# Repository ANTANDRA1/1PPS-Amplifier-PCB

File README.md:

# 1PPS-Amplifier-PCB
1PPS signal buffer/inverter PCB for u-blox M8N GPS with 50 Ohm output
# Плата підсилення сигналу 1PPS

Плата призначена для буферизації та інвертування сигналу **1PPS від GPS-приймача u-blox M8N**.

Плата приймає логічний сигнал 1PPS від GPS-модуля, буферизує та інвертує його за допомогою логічного інвертора **74LVC1G04**, після чого передає сигнал на вихід через **BNC-роз’єм з узгодженням під 50 Ом**.

## Основні можливості

- вхід сигналу 1PPS від GPS-приймача;
- живлення 3.3 В;
- швидкодіючий логічний інвертор 74LVC1G04;
- інвертований вихід 1PPS;
- послідовне узгодження виходу для роботи з 50-омною лінією;
- вихід через BNC female PCB;
- вхід через Dupont 2.54 мм;
- роз’єм живлення Dupont 2.54 мм;
- розв’язувальний конденсатор 100 нФ;
- одностороння розводка плати;
- полігон GND;
- монтажні отвори під гвинти M2;
- підписи роз’ємів і контактів на шовкографії плати.

## Сигнальний тракт

```text
GPS 1PPS
   |
   v
J1 - 1PPS IN
   |
R1 - 100 Ом
   |
U1 - 74LVC1G04
   |
R2 - 33 Ом
   |
J4 - BNC 1PPS OUT
```

Мікросхема **74LVC1G04** виконує буферизацію та інвертування сигналу.

Резистор R2 використовується для послідовного узгодження виходу. Разом із власним вихідним опором логічного драйвера він формує вихід, придатний для підключення до лінії з хвильовим опором 50 Ом.

## Живлення

Плата живиться від напруги **3.3 В**.

Роз’єм живлення J2:

| Контакт | Сигнал |
|---|---|
| 1 | +3.3 V |
| 2 | GND |

Біля мікросхеми U1 встановлений розв’язувальний конденсатор **C1 100 нФ**.

## Роз’єми

### J1 — вхід 1PPS

Роз’єм Dupont 2.54 мм на 2 контакти.

| Контакт | Сигнал |
|---|---|
| 1 | 1PPS_IN |
| 2 | GND |

### J2 — вхід живлення

Роз’єм Dupont 2.54 мм на 2 контакти.

| Контакт | Сигнал |
|---|---|
| 1 | +3.3 V |
| 2 | GND |

### J4 — вихід 1PPS

BNC female PCB.

- центральний контакт — `1PPS_OUT`;
- екран — `GND`;
- номінальний імпеданс інтерфейсу — 50 Ом.

## Основні компоненти

| Позначення | Компонент | Номінал / тип |
|---|---|---|
| U1 | Логічний інвертор | 74LVC1G04 |
| R1 | Резистор | 100 Ом |
| R2 | Вихідний послідовний резистор | 33 Ом |
| C1 | Розв’язувальний конденсатор | 100 нФ |
| J1 | Вхід 1PPS | Dupont 2.54 мм, 2 контакти |
| J2 | Вхід живлення | Dupont 2.54 мм, 2 контакти |
| J4 | Вихід 1PPS | BNC female PCB, 50 Ом |

## Друкована плата

Плата розроблена у **KiCad**.

Поточна версія має **односторонню розводку**.

Сигнальні доріжки, доріжки живлення та полігон землі розміщені на одному мідному шарі.

Використані ширини доріжок:

- сигнал 1PPS — приблизно 0.30 мм;
- вихідний сигнал 1PPS — приблизно 0.30–0.40 мм;
- живлення 3.3 В — приблизно 0.50 мм;
- GND — полігон землі.

Доріжки між **U1, R2 та BNC-роз’ємом** виконані максимально короткими для зменшення спотворень сигналу.

Конденсатор C1 розташований максимально близько до U1.

На платі також передбачені монтажні отвори під **гвинти M2**.

## Структура репозиторію

```text
1PPS-Amplifier-PCB/
│
├── README.md
│
├── KiCad/
│   ├── *.kicad_pro
│   ├── *.kicad_sch
│   └── *.kicad_pcb
│
├── Gerber/
│   ├── *.gbr
│   └── *.drl
│
├── Documentation/
│   └── schematic.pdf
│
└── Images/
    ├── schematic.png
    ├── pcb_layout.png
    └── 3d_view.png
```

## Відтворення проєкту

### 1. Встановлення KiCad

Необхідно встановити сумісну версію KiCad.

### 2. Завантаження репозиторію

Репозиторій можна клонувати командою:

```bash
git clone <посилання-на-репозиторій>
```

Або завантажити архів ZIP безпосередньо з GitHub.

### 3. Відкриття проєкту

Необхідно відкрити файл:

```text
*.kicad_pro
```

у папці `KiCad`.

Проєкт містить:

- принципову схему;
- розводку друкованої плати;
- посадочні місця компонентів;
- електричні з’єднання;
- контур плати.

### 4. Перевірка принципової схеми

У Schematic Editor необхідно перевірити сигнальний тракт:

```text
1PPS_IN -> R1 -> U1 -> R2 -> 1PPS_OUT
```

Живлення:

```text
3.3 V -> U1
      -> C1
```

Перед переходом до PCB необхідно запустити **Electrical Rules Checker (ERC)**.

### 5. Перевірка друкованої плати

У PCB Editor необхідно перевірити:

- розташування компонентів;
- трасування доріжок;
- полігон GND;
- розташування BNC-роз’єму;
- монтажні отвори M2;
- підписи на шовкографії.

Перед виготовленням необхідно запустити **Design Rules Checker (DRC)**.

## Підготовка файлів для виробництва

Gerber-файли формуються у KiCad через:

```text
File -> Plot
```

Файли свердління формуються через:

```text
Generate Drill Files
```

Отримані виробничі файли необхідно зберегти у папці:

```text
Gerber/
```

## Перевірка готової плати

Після монтажу компонентів:

1. Подати живлення 3.3 В на J2.
2. Підключити вихід 1PPS GPS-приймача u-blox M8N до J1.
3. Підключити осцилограф до BNC-виходу J4.
4. Перевірити наявність одного імпульсу за секунду.
5. Порівняти сигнал на вході та виході плати.
6. Переконатися, що вихідний сигнал інвертований.
7. Перевірити фронт і спад вихідного імпульсу.
8. Переконатися у відсутності значних спотворень сигналу.

## Призначення проєкту

Метою проєкту є розробка компактної друкованої плати, яка приймає сигнал синхронізації **1PPS від GPS-приймача**, буферизує та інвертує його і формує зручний BNC-вихід для підключення зовнішнього вимірювального або синхронізуючого обладнання.

Проєкт містить усі основні файли, необхідні для відкриття, перевірки, редагування та повторного виготовлення плати.

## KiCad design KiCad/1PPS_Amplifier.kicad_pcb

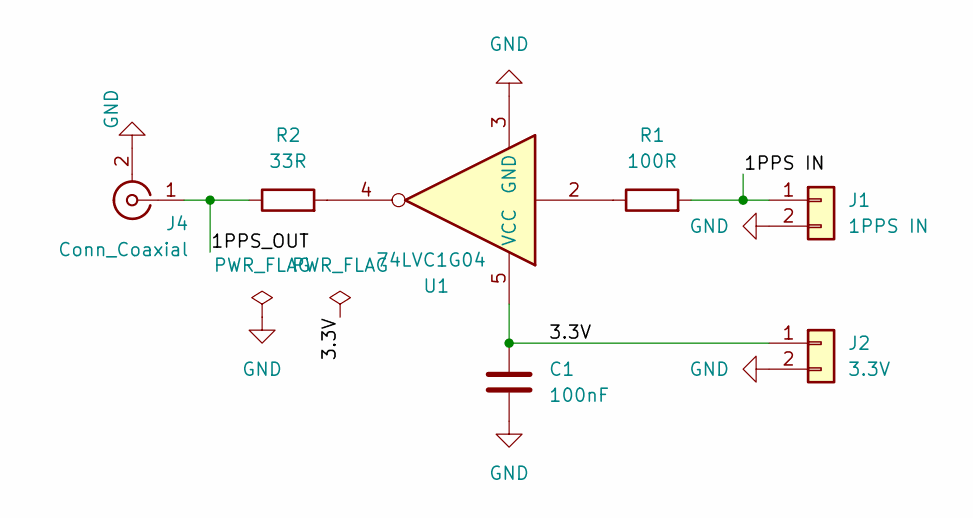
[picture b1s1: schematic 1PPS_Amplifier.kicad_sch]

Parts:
C1: 100nF; C_0805_2012Metric
J1: 1PPS IN; PinHeader_1x02_P2.54mm_Vertical
J2: 3.3V; PinHeader_1x02_P2.54mm_Vertical
J4: Conn_Coaxial; BNC_Amphenol_B6252HB-NPP3G-50_Horizontal
R1: 100R; R_0805_2012Metric
R2: 33R; R_0805_2012Metric
U1: 74LVC1G04; SOT-23-5

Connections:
/1PPS IN: J1.1, R1.2
/1PPS_OUT: J4.1 (In), R2.1
/3.3V: C1.1, J2.1, U1.5 (VCC)
GND: C1.2, J1.2, J2.2, J4.2 (Ext), U1.3 (GND)
unnamed: R1.1, U1.2
unnamed: R2.2, U1.4

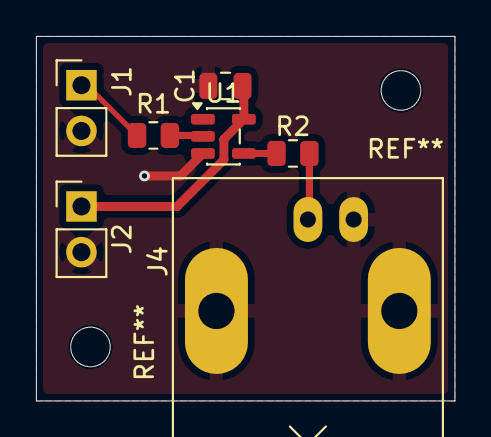
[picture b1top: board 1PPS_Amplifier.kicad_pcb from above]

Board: 2 copper layers, 23.2 x 20.2 mm, 7 parts (0 on the bottom side), 6 nets.
